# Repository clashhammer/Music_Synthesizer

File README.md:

# Music_Synthesizer
A project that studies the effect of sound and how waves produce it. Works like a piano and has a screen that outputs like a digital oscilloscope showing the wave that you hear and telling you it's frequency.

I got the idea from a girl I know that wants to be a singer and she said she wanted to buy a synthesizer to get a step closer to composing her own song. That's when I thought "how cool it would be to try and make one, maybe even give it to her if it turns out good.". And yeah, that's basically how I got an idea to build a musical synthesizer.

## Bill of Materials

| Part | Quantity | Price | Link |
|---|---:|---:|---|
| ESP32 DevKit V1 | 1 | €6.89 | [Buy](https://share.temu.com/K3tj6sE6siB) |
| PCM5102 DAC Module | 2 | €2.65 | [Buy](https://a.aliexpress.com/_ExivHVu) |
| XH-A156 Amplifier Board | 1 | €1.29 | [Buy](https://a.aliexpress.com/_EQBbn1Y) |
| 2W 8Ω Speaker | 4 | €2.16 | [Buy](https://a.aliexpress.com/_EGUYYXC) |
| SN74HC595N Shift Register | 1 | €1.93 | [Buy](https://a.aliexpress.com/_EvkP7yO) |
| GMT020-02-8P TFT Display | 1 | — | Any compatible ST7789 TFT display should work |
| Push Button | 26 | — | Any suitable push button set should work |
| 1N4148 Diode | 24 | €3.86 | [Buy](https://share.temu.com/MGWPABEpR8B) |
| 10kΩ Resistor | 4 | €0.87 | [Buy](https://share.temu.com/5ZgNjFWWyZB) |
| 100nF Ceramic Capacitor | 1 | — | Any 100 nF ceramic capacitor should work |

To build a prototype follow the schematic and see where each wire is connected then upload the code to the ESP32 to use it. My own prototype uses just one custom PAM 8403 amplifier board and just one PCM5102 DAC board. I have color coded and connected all parts adjusting to the pinout and code in the schematic for easy understanding.

Also for the code you'll need to download some libraries from the ARDUINO IDE library picker for the code to propperly compile. These are:
- ESP_I2S (should be the second one in the list)
- Adafruit_GFX (again should be second one)
- Adafruit_ST7789 (first one this time)

I also have some custom part signs that I've uploaded as a rar file.

Btw if you haven't used ESP32 before (like me), to connect it to your computer and upload the code you need to install a driver, corelating to what your ESP32 type is. There is a little chip under the big one on the board. To install the correct drivers you need to see what the letters on this chip say. If they say "SILABS CP210x" you need to install the CP210x driver. If it says "CH340" you need to install the CH340 driver on your computer. if it says nothing you need to install the CH340 driver.

Here are the links to both drivers' sites
- CP210x - https://www.silabs.com/software-and-tools/usb-to-uart-bridge-vcp-drivers?tab=overview

- CH340 - https://www.wch-ic.com/downloads/CH341SER_EXE.html

Here are some photos of the finished part of the project like schematic, pcb and 3D display of it and youtube video of how it works.

Youtube video (unlisted): https://youtube.com/shorts/R9iYHdPvPAw

This isn't final and I'll make more updates in the future, thus the not so explanatory explanations.

I added an MIT Licence for free use of my project files.

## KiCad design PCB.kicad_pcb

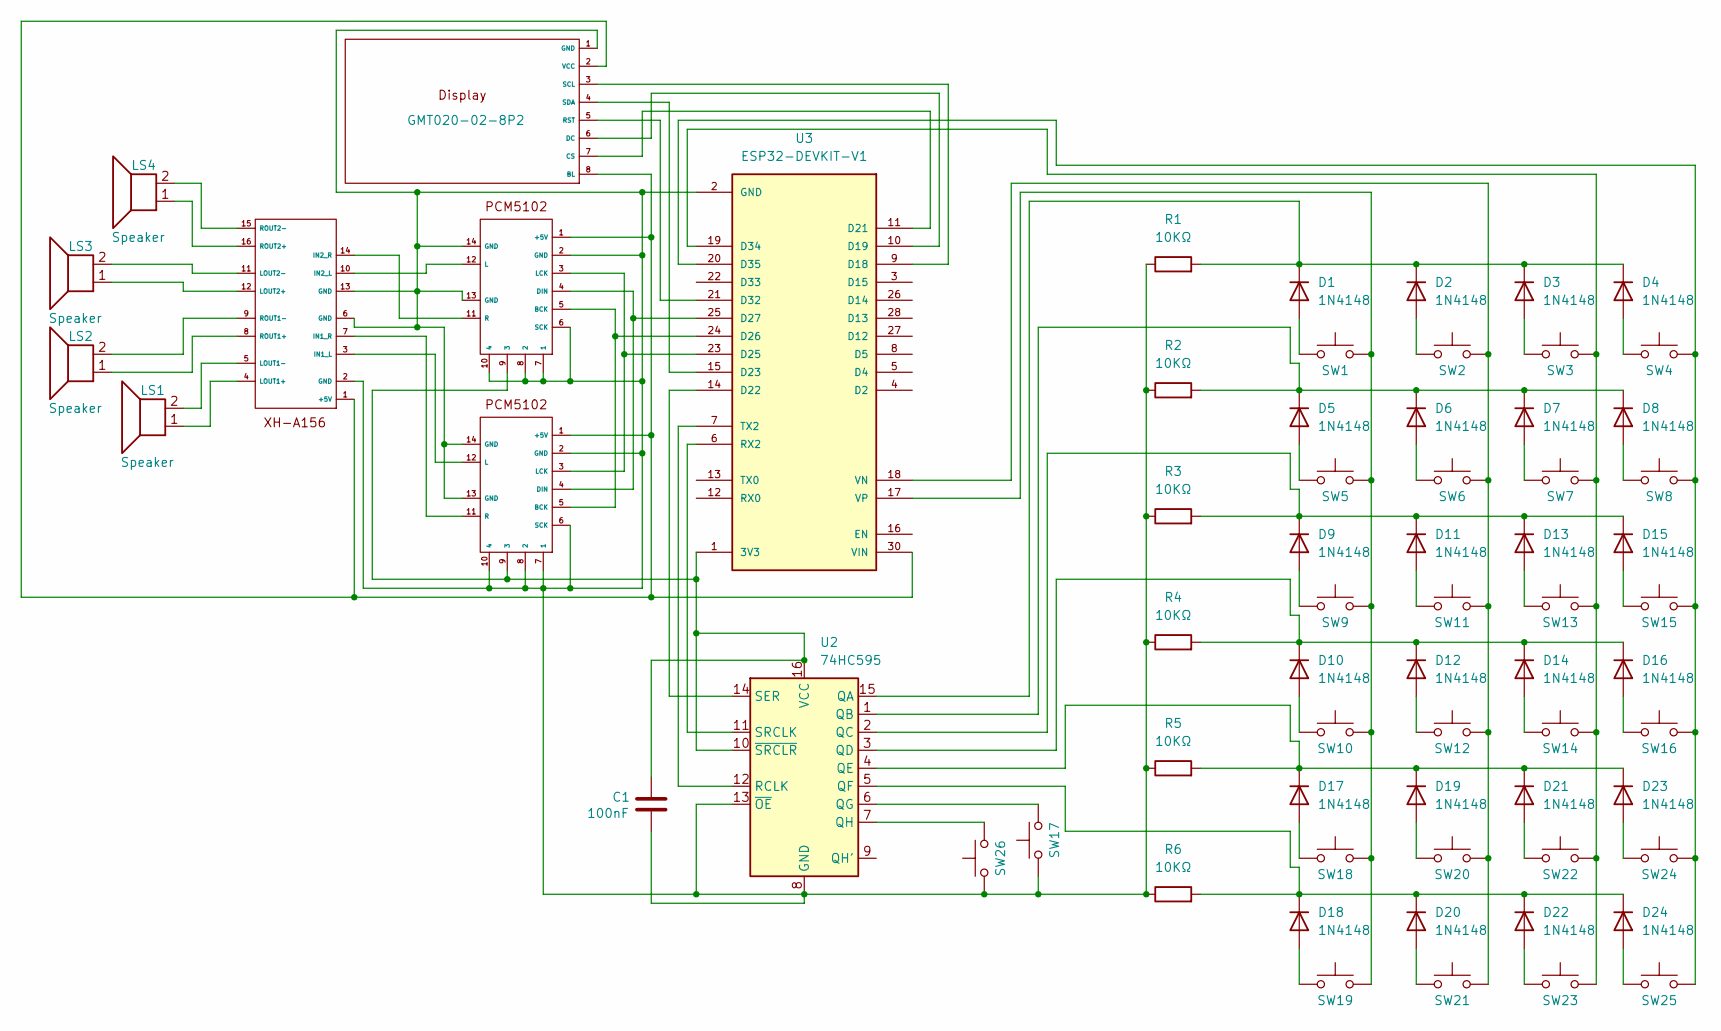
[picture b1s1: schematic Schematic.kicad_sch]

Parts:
C1: 100nF; C_Disc_D5.0mm_W2.5mm_P5.00mm
D1, D2, D3, D4, D5, D6, D7, D8, D9, D10, D11, D12, D13, D14, D15, D16, D17, D18, D19, D20, D21, D22, D23, D24: 1N4148; D_DO-35_SOD27_P7.62mm_Horizontal
GMT020-02-8P2: GMT020-02-8P
LS1, LS2, LS3, LS4: Speaker; PinHeader_1x02_P2.54mm_Horizontal
PCM1, PCM3: PCM5102
R1, R2, R3, R4, R5, R6: 10KΩ; R_Axial_DIN0207_L6.3mm_D2.5mm_P7.62mm_Horizontal
SW1, SW2, SW3, SW4, SW5, SW6, SW7, SW8, SW9, SW10, SW11, SW12, SW13, SW14, SW15, SW16, SW18, SW19, SW20, SW21, SW22, SW23, SW24, SW25: SW_Push; SW_PUSH-12mm
SW17, SW26: SW_Push; SW_PUSH_6mm
U2: 74HC595; DIP-16_W7.62mm
U3: ESP32-DEVKIT-V1; MODULE_ESP32_DEVKIT_V1; PARTREV N/A
XH-A1: XH-A156 4-way amplifier board

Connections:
GND: C1.2, GMT020-02-8P2.1 (GND), PCM1.2 (GND), PCM1.6 (SCK), PCM1.7 (1), PCM1.8 (2), PCM1.10 (4), PCM1.13 (GND), PCM1.14 (GND), PCM3.2 (GND), PCM3.6 (SCK), PCM3.7 (1), PCM3.8 (2), PCM3.10 (4), PCM3.13 (GND), PCM3.14 (GND), R1.1, R2.1, R3.1, R4.1, R5.1, R6.1, SW17.1, SW26.1, U2.8 (GND), U2.13 (~OE), U3.2 (GND), U3.29 (GND), XH-A1.2 (GND), XH-A1.6 (GND), XH-A1.13 (GND)
unnamed: D1.2 (A), SW1.1
unnamed: D1.1 (K), D2.1 (K), D3.1 (K), D4.1 (K), R1.2, U2.15 (QA)
unnamed: D2.2 (A), SW2.1
unnamed: D3.2 (A), SW3.1
unnamed: D4.2 (A), SW4.1
unnamed: D5.2 (A), SW5.1
unnamed: D5.1 (K), D6.1 (K), D7.1 (K), D8.1 (K), R2.2, U2.1 (QB)
unnamed: D6.2 (A), SW6.1
unnamed: D7.2 (A), SW7.1
unnamed: D8.2 (A), SW8.1
unnamed: D9.2 (A), SW9.1
unnamed: D10.2 (A), SW10.1
unnamed: D10.1 (K), D12.1 (K), D14.1 (K), D16.1 (K), R4.2, U2.3 (QD)
unnamed: D11.2 (A), SW11.1
unnamed: D9.1 (K), D11.1 (K), D13.1 (K), D15.1 (K), R3.2, U2.2 (QC)
unnamed: D12.2 (A), SW12.1
unnamed: D13.2 (A), SW13.1
unnamed: D14.2 (A), SW14.1
unnamed: D15.2 (A), SW15.1
unnamed: D16.2 (A), SW16.1
unnamed: D17.2 (A), SW18.1
unnamed: D17.1 (K), D19.1 (K), D21.1 (K), D23.1 (K), R5.2, U2.4 (QE)
unnamed: D18.2 (A), SW19.1
unnamed: D18.1 (K), D20.1 (K), D22.1 (K), D24.1 (K), R6.2, U2.5 (QF)
unnamed: D19.2 (A), SW20.1
unnamed: D20.2 (A), SW21.1
unnamed: D21.2 (A), SW22.1
unnamed: D22.2 (A), SW23.1
unnamed: D23.2 (A), SW24.1
unnamed: D24.2 (A), SW25.1
unnamed: GMT020-02-8P2.2 (VCC), GMT020-02-8P2.8 (BL), PCM1.1 (+5V), PCM3.1 (+5V), U3.30 (VIN), XH-A1.1 (+5V)
unnamed: GMT020-02-8P2.7 (CS), U3.11 (D21)
unnamed: GMT020-02-8P2.6 (DC), U3.10 (D19)
unnamed: GMT020-02-8P2.5 (RST), U3.21 (D32)
unnamed: GMT020-02-8P2.3 (SCL), U3.9 (D18)
unnamed: GMT020-02-8P2.4 (SDA), U3.15 (D23)
unnamed: C1.1, PCM1.9 (3), PCM3.9 (3), U2.10 (~SRCLR), U2.16 (VCC), U3.1 (3V3)
unnamed: PCM1.5 (BCK), PCM3.5 (BCK), U3.24 (D26)
unnamed: PCM1.4 (DIN), PCM3.4 (DIN), U3.25 (D27)
unnamed: PCM1.12 (L), XH-A1.10 (IN2_L)
unnamed: PCM1.3 (LCK), PCM3.3 (LCK), U3.23 (D25)
unnamed: PCM1.11 (R), XH-A1.14 (IN2_R)
unnamed: PCM3.12 (L), XH-A1.3 (IN1_L)
unnamed: PCM3.11 (R), XH-A1.7 (IN1_R)
unnamed: SW17.2, U2.6 (QG)
unnamed: SW26.2, U2.7 (QH)
unnamed: U2.12 (RCLK), U3.7 (TX2)
unnamed: U2.14 (SER), U3.14 (D22)
unnamed: U2.11 (SRCLK), U3.6 (RX2)
unnamed: SW3.2, SW7.2, SW13.2, SW14.2, SW22.2, SW23.2, U3.19 (D34)
unnamed: SW4.2, SW8.2, SW15.2, SW16.2, SW24.2, SW25.2, U3.20 (D35)
unnamed: SW2.2, SW6.2, SW11.2, SW12.2, SW20.2, SW21.2, U3.18 (VN)
unnamed: SW1.2, SW5.2, SW9.2, SW10.2, SW18.2, SW19.2, U3.17 (VP)
unnamed: LS1.1, XH-A1.4 (LOUT1+)
unnamed: LS1.2, XH-A1.5 (LOUT1-)
unnamed: LS3.1, XH-A1.12 (LOUT2+)
unnamed: LS3.2, XH-A1.11 (LOUT2-)
unnamed: LS2.1, XH-A1.8 (ROUT1+)
unnamed: LS2.2, XH-A1.9 (ROUT1-)
unnamed: LS4.1, XH-A1.16 (ROUT2+)
unnamed: LS4.2, XH-A1.15 (ROUT2-)

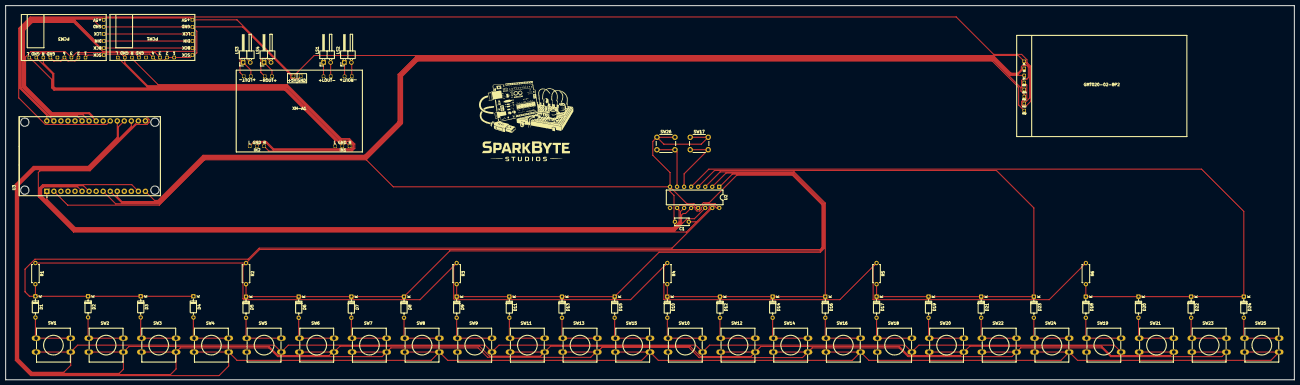
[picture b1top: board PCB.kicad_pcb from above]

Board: 2 copper layers, 465.0 x 135.0 mm, 67 parts (0 on the bottom side), 62 nets.

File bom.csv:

Part,Quantity,Price,Link
ESP32 DevKit V1,1,€6,89,https://share.temu.com/K3tj6sE6siB
PCM5102 DAC Module,2,€2,65,https://a.aliexpress.com/_ExivHVu
XH-A156 Amplifier Board,1,€1.29,https://a.aliexpress.com/_EQBbn1Y
2W 8Ω Speaker,4,€2.16,https://a.aliexpress.com/_EGUYYXC
SN74HC595N Shift Register,1,€1.93,https://a.aliexpress.com/_EvkP7yO
GMT020-02-8P TFT Display,1,,can't find a link, any ST7789 TFT display should work.
Push Button,26,,can't find link, any push button set should work
1N4148 Diode,24,€3,86,https://share.temu.com/MGWPABEpR8B
10k Ohm Resistor,4,€0,87,https://share.temu.com/5ZgNjFWMyZB
100nF Ceramic Capacitor,1,,can't find a direct link, any 100 nF ceramic capacitor should work.

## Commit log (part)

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2026-04-07 Sine wave project details
    Pinout and instructions
2026-04-07 Sine wave output code
2026-04-07 Pinout and instructions for Sine wave output code.
    Everything you need for this project and how to connect it. This is only the start ;)
2026-04-15 Output for 4 different types of waves.
2026-04-15 What you need for the project and changes
    Added information about Week 2 code and testing requirements.
2026-04-15 What you need for the project and changes
2026-04-21 Code for the 4 types of waves
2026-04-21 What you need for the project and changes
    Added links to YouTube videos for Week 1 and Week 2.
2026-04-21 Output of 4 different kinds of waves
2026-04-21 Output of 4 different kinds of waves.
2026-04-22 Details of the project, what you need to make it yourself
    Added details about Week 3 progress and requirements for the musical output project.
2026-04-22 Musical output of waves.
    Really cool!
